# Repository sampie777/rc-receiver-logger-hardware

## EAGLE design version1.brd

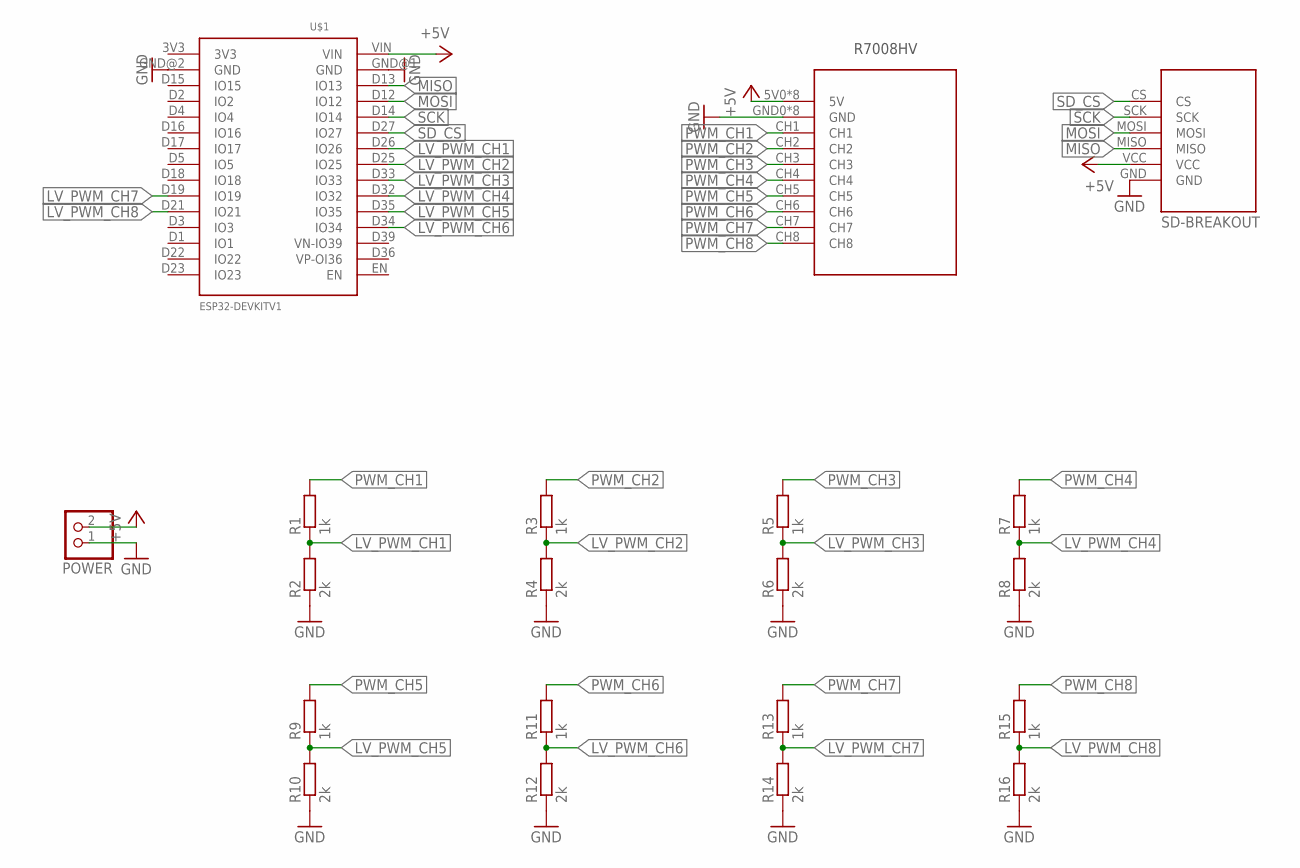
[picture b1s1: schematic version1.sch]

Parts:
POWER: PINHD-1X2; 1X02
R1, R3, R5, R7, R9, R11, R13, R15: 1k; 0207/7
R2, R4, R6, R8, R10, R12, R14, R16: 2k; 0207/7
U$1: ESP32DEVKITV1; ESP32-DEVKITV1
U$2: HKD-MICRO-SD-BREAKOUTV; HKD-MICRO-SD-BREAKOUT-VERTICAL
U$3: R7008HV

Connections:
+5V: POWER.2, U$1.VIN, U$2.VCC, U$3.5V0 (5V), U$3.5V1 (5V), U$3.5V2 (5V), U$3.5V3 (5V), U$3.5V4 (5V), U$3.5V5 (5V), U$3.5V6 (5V), U$3.5V7 (5V)
GND: POWER.1, R2.1, R4.1, R6.1, R8.1, R10.1, R12.1, R14.1, R16.1, U$1.GND@1 (GND), U$1.GND@2 (GND), U$2.GND, U$3.GND0 (GND), U$3.GND1 (GND), U$3.GND2 (GND), U$3.GND3 (GND), U$3.GND4 (GND), U$3.GND5 (GND), U$3.GND6 (GND), U$3.GND7 (GND)
LV_PWM_CH1: R1.1, R2.2, U$1.D26 (IO26)
LV_PWM_CH2: R3.1, R4.2, U$1.D25 (IO25)
LV_PWM_CH3: R5.1, R6.2, U$1.D33 (IO33)
LV_PWM_CH4: R7.1, R8.2, U$1.D32 (IO32)
LV_PWM_CH5: R9.1, R10.2, U$1.D35 (IO35)
LV_PWM_CH6: R11.1, R12.2, U$1.D34 (IO34)
LV_PWM_CH7: R13.1, R14.2, U$1.D19 (IO19)
LV_PWM_CH8: R15.1, R16.2, U$1.D21 (IO21)
MISO: U$1.D13 (IO13), U$2.MISO
MOSI: U$1.D12 (IO12), U$2.MOSI
PWM_CH1: R1.2, U$3.CH1
PWM_CH2: R3.2, U$3.CH2
PWM_CH3: R5.2, U$3.CH3
PWM_CH4: R7.2, U$3.CH4
PWM_CH5: R9.2, U$3.CH5
PWM_CH6: R11.2, U$3.CH6
PWM_CH7: R13.2, U$3.CH7
PWM_CH8: R15.2, U$3.CH8
SCK: U$1.D14 (IO14), U$2.SCK
SD_CS: U$1.D27 (IO27), U$2.CS

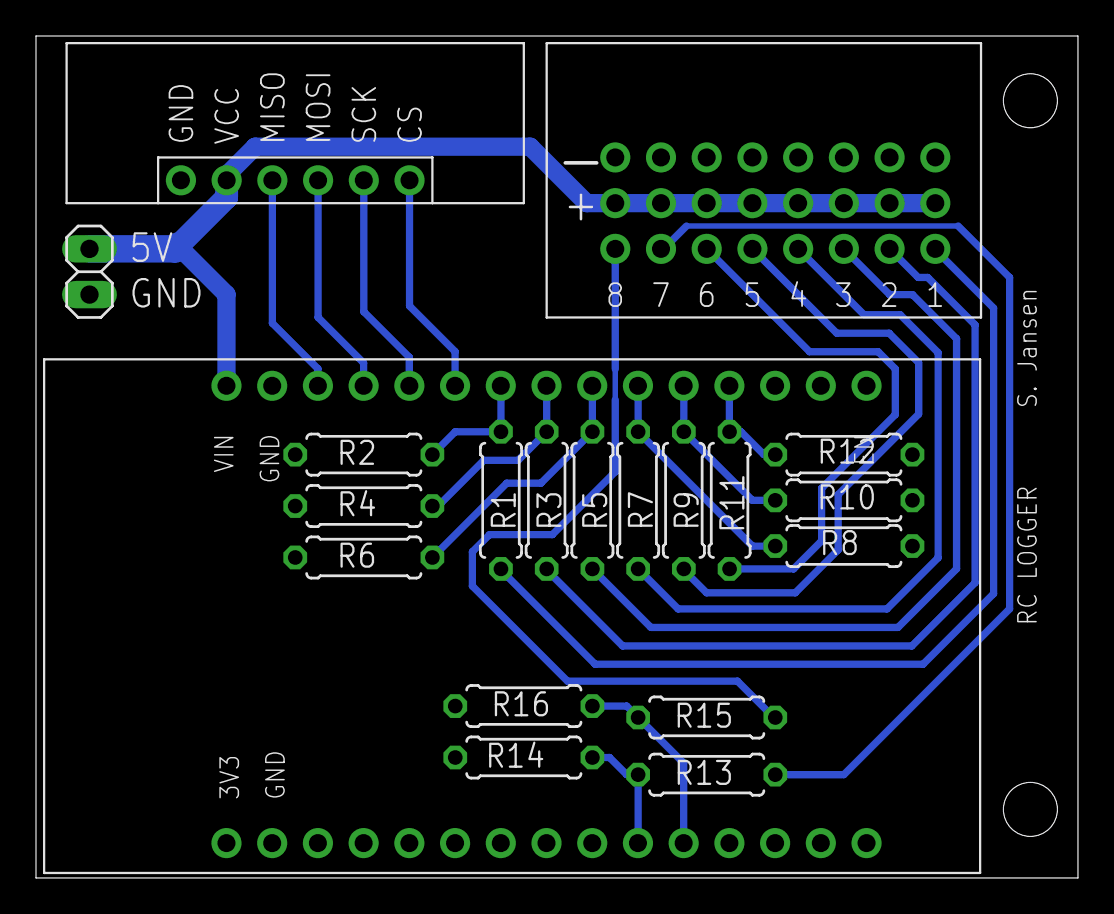
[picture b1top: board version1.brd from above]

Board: 2 copper layers, 57.9 x 46.8 mm, 20 parts (0 on the bottom side), 22 nets.
